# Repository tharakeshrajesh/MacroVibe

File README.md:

# MacroVibe
A lazily made macropad that doesn't use a key matrix and has one rotary encoder.

### Schematics and PCB

Both were made in KiCad 9.0, highly recommend, will use from now on.

### Case

This case was made in Fusion360, I spent most of the time on this stupid case than any other part of the project because the keyholes and other holes would not line up
so I had to try like 5 times before I kind of got it.

### Firmware

Firmware was coded using KMK so you will need a program to flash your RP2040.
Keycodes/macros are not set in the code so you will have to manually set those in main.py.

### Setup
1. Get the cases and PCB printed and order the parts.
2. Solder the parts onto the PCB.
3. Assemble the PCB and case.
4. Flash your edited main.py onto the RP2040.
5. Pray and test.

## BOM
| Item | Quantity | Average cost (USD)|
|:----------:|:----------:|:----------:|
|XIAO RP2040 DIP|x1|~$4|
|Cherry MX Switches|x7|~$5|
|SK6812 MINI LEDs|x2|~$3|
|Blank DSA Keycaps|x7|~$6|
|M3x16 Bolt|x4|~$2|
|M3 Heatset|x4|~$1|
|Alps EC11E Rotary Encoder|x1|~$2|
|PCB|x1|~$3|
|3D printed top case|x1|~$2|
|3D printed bottom case|x1|~$2|
|Total||~$30|

### Credits
* Encoder knob was made by [void](https://www.printables.com/@void) on [printables](https://www.printables.com). Page [here](https://www.printables.com/model/347536-encoder-knob).
* Special thanks to alexren and qcoral for making a guide on how to make a hackpad. Page [here](https://hackpad.hackclub.com).

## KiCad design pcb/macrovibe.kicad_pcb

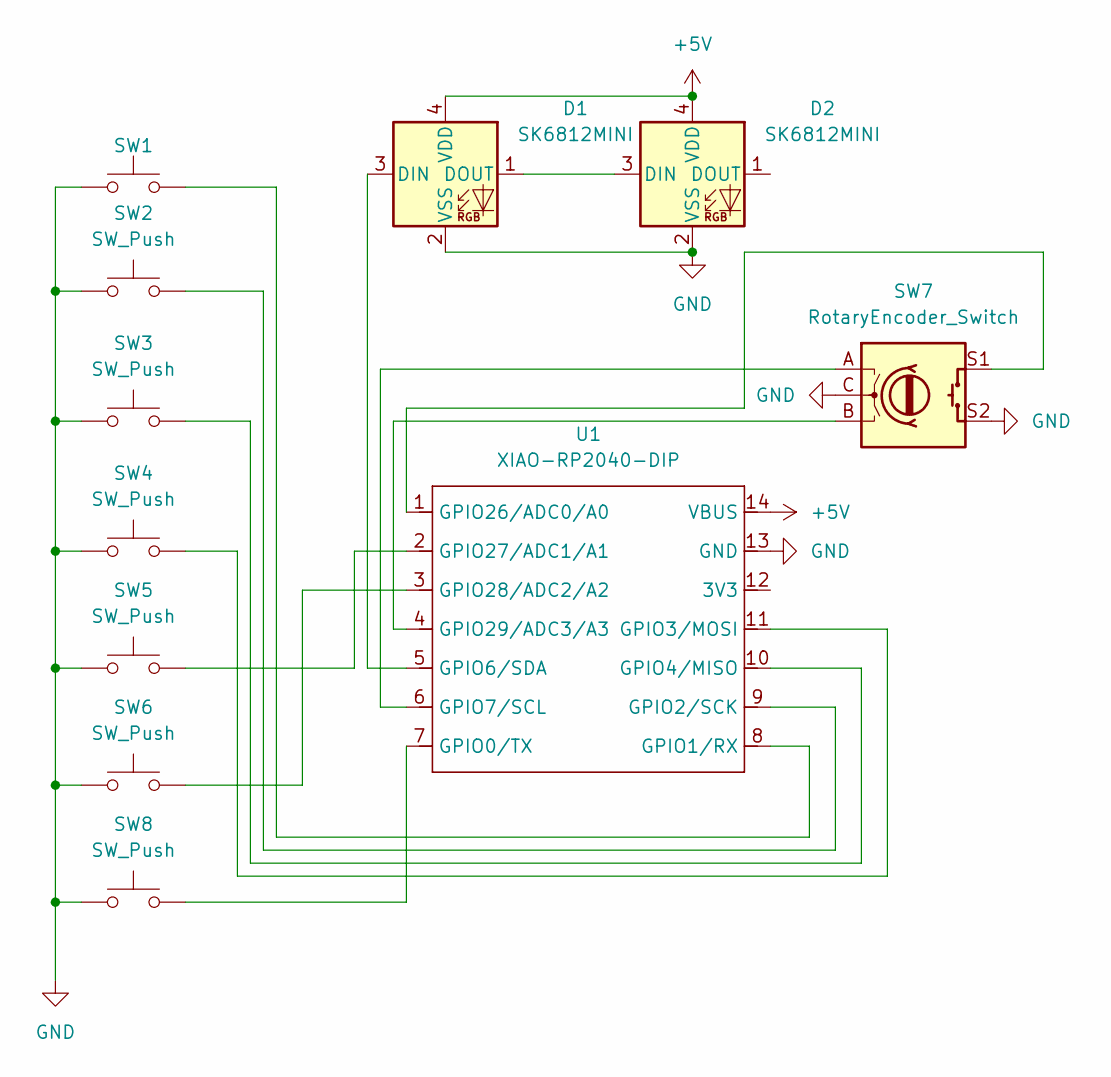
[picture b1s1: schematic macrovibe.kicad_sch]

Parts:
D1, D2: SK6812MINI; LED_SK6812MINI_PLCC4_3.5x3.5mm_P1.75mm
SW1, SW2, SW3, SW4, SW5, SW6, SW8: SW_Push; SW_Cherry_MX_1.00u_PCB
SW7: RotaryEncoder_Switch; RotaryEncoder_Alps_EC11E-Switch_Vertical_H20mm
U1: XIAO-RP2040-DIP

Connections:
+5V: D1.4 (VDD), D2.4 (VDD), U1.14 (VBUS)
GND: D1.2 (VSS), D2.2 (VSS), SW1.1, SW2.1, SW3.1, SW4.1, SW5.1, SW6.1, SW7.C, SW7.S2, SW8.1, U1.13 (GND)
unnamed: D1.3 (DIN), U1.5 (GPIO6/SDA)
unnamed: D1.1 (DOUT), D2.3 (DIN)
unnamed: SW8.2, U1.7 (GPIO0/TX)
unnamed: SW1.2, U1.8 (GPIO1/RX)
unnamed: SW2.2, U1.9 (GPIO2/SCK)
unnamed: SW4.2, U1.11 (GPIO3/MOSI)
unnamed: SW3.2, U1.10 (GPIO4/MISO)
unnamed: SW7.A, U1.6 (GPIO7/SCL)
unnamed: SW7.S1, U1.1 (GPIO26/ADC0/A0)
unnamed: SW5.2, U1.2 (GPIO27/ADC1/A1)
unnamed: SW6.2, U1.3 (GPIO28/ADC2/A2)
unnamed: SW7.B, U1.4 (GPIO29/ADC3/A3)

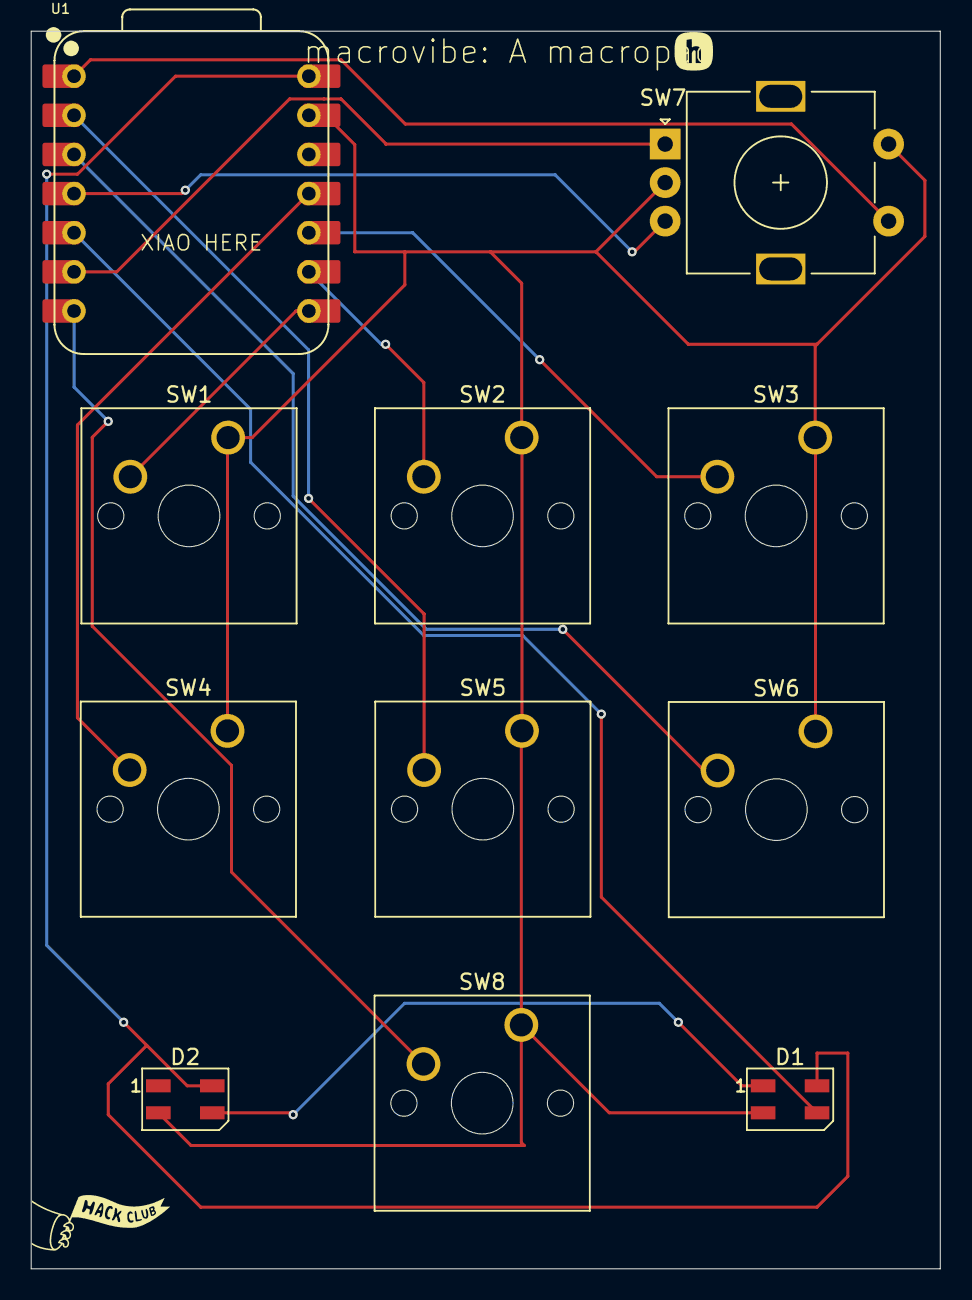
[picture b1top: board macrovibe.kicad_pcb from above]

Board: 2 copper layers, 59.0 x 80.3 mm, 11 parts (0 on the bottom side), 14 nets.

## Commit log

2025-06-25 Update LICENSE
2025-06-27 v1
    too much time spent...
2025-06-28 Added encoder knobs
    Credits to https://www.printables.com/model/347536-encoder-knob
